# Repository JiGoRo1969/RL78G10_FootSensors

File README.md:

# FootSensors with RL78/G10 software library (Rev.20200416)

This is a project to use Force Sensing Registors with RL78/G10
included with CS+ environment setting files provided by Renesas Electronics Corp.
So you can easily modify and add this codes with CS+ on Windows PC.
  
Let's enjoy it !

## Information for target board

RL78/G10 board "AE-R5F10Y47ASP" is provided by Akizukidenshi in Japan.
  
JPN : http://akizukidenshi.com/catalog/g/gK-09035/

## Installation

Import this project into CS+.

## Usage

The protocol stack is defined with an ICS3.5 provided by KONDO Kagaku.
ICS3.5 uses "Data=8bit, Stop=1bit, Parity=EVEN, baudrate=1.5Mbps."
You will get 4 sensor unit data when master MCU/MPU send 4 bytes data as follows :
|Command|SC|Address|Length|
|-------|--|-------|------|
|0xA0+ID|0x7F|0(fiexed)|4(fiexed)|
  
ID is defined as D_MY_ID in "cg_src/r_cg_userdefine.h".

## Current Support Peripherals

|Function Name        | Pin Name        | notes |
|:--------------------|:---------------:|:------|
|Analog Input         |P02/ANI1         | connecting to one of Force Sensing Registor with pulled up to 3.3V | 
|Analog Input         |P03/ANI2         | connecting to one of Force Sensing Registor with pulled up to 3.3V | 
|Analog Input         |P04/ANI3         | connecting to one of Force Sensing Registor with pulled up to 3.3V | 
|Analog Input         |P05/ANI4         | connecting to one of Force Sensing Registor with pulled up to 3.3V | 
|UART I/F             |P00/TxD0         | connecting to RxD of master MCU/MPU | 
|UART I/F             |P01/RxD0         | connecting to TxD of master MCU/MPU | 
|X'tal                |X1,X2            | mounted on board |
|OCD Debugger I/F     |RESET, TOOL0     | connecting to DEBUGGER |
|Non Connections      |P06, P07, P41    | |
  
You can refer CAD data with Eagle(.brd and .sch) to understand the circuit.
  
|File Name | purpose |
|:--------:|:-------:|
|RL78G10_FOOT_A2.brd| PCB pattern data for pressure sensors with R5F10Y47ASP|
|RL78G10_FOOT_A2.sch| circuit data |
|--------|-------|
|RL78G10_E1.brd| PCB pattern data connecting to E1/E2/E2Lite |
|RL78G10_E1.sch| circuit data |

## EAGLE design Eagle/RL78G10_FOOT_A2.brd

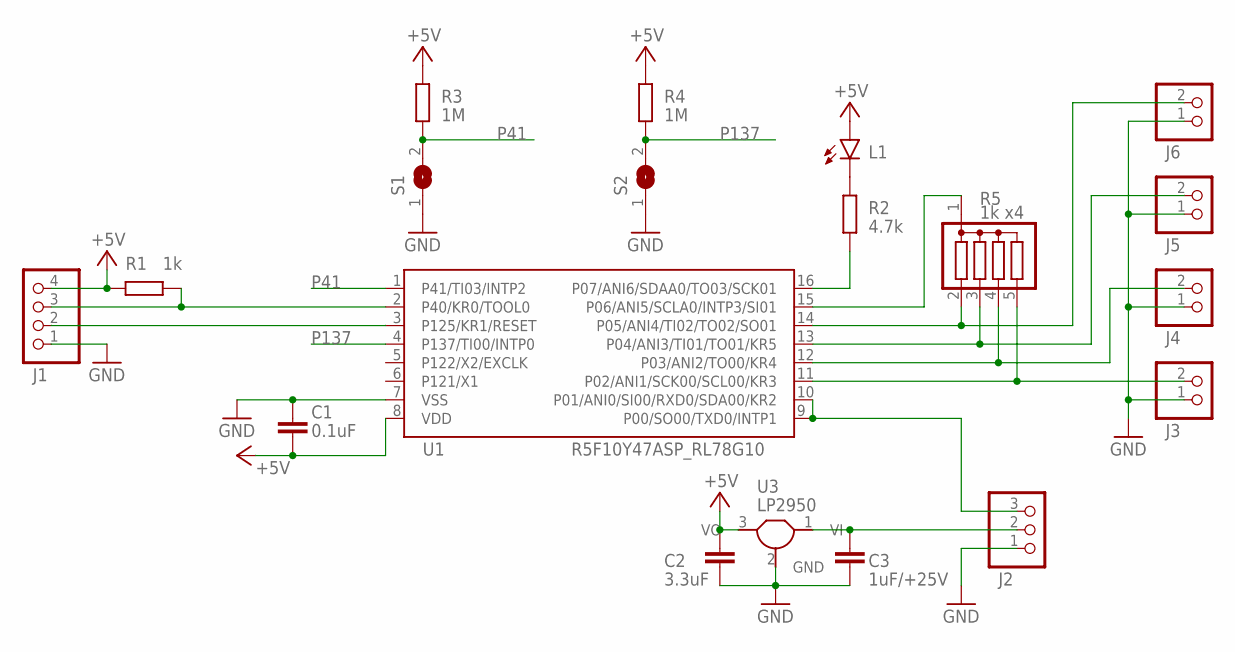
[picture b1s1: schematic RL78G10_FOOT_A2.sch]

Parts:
C1: 0.1uF; C0603
C2: 3.3uF; C0805
C3: 1uF/+25V; C0805
J1: PINHD_1X4; PINHD_1X04
J2: PINHD_1X3; PINHD_1X03
J3, J4, J5, J6: PINHD_1X2; PINHD_1X02
L1: LEDSML0603; SML0603
R1: 1k; R0603
R2: 4.7k; R0603
R3, R4: 1M; R0603
R5: 1k x4; SIL5
S1, S2: SJ-OMINI; SJ-O
U1: R5F10Y47ASP_RL78G10; SSOP16
U3: LP2950; TO92-

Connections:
+5V: C1.2, C2.1, J1.4, L1.A, R1.1, R3.1, R4.1, U1.8 (VDD), U3.3 (VO)
+V: C3.1, J2.2, U3.1 (VI)
ANI1: J3.2, R5.5, U1.11 (P02/ANI1/SCK00/SCL00/KR3)
ANI2: J4.2, R5.4, U1.12 (P03/ANI2/TO00/KR4)
ANI3: J5.2, R5.3, U1.13 (P04/ANI3/TI01/TO01/KR5)
ANI4: J6.2, R5.2, U1.14 (P05/ANI4/TI02/TO02/SO01)
GND: C1.1, C2.2, C3.2, J1.1, J2.1, J3.1, J4.1, J5.1, J6.1, S1.1, S2.1, U1.7 (VSS), U3.2 (GND)
LED: L1.C, R2.1
P06: R5.1, U1.15 (P06/ANI5/SCLA0/INTP3/SI01)
P41: R3.2, S1.2, U1.1 (P41/TI03/INTP2)
P137: R4.2, S2.2, U1.4 (P137/TI00/INTP0)
RESET: J1.2, U1.3 (P125/KR1/RESET)
SIG: J2.3, U1.9 (P00/SO00/TXD0/INTP1), U1.10 (P01/ANI0/SI00/RXD0/SDA00/KR2)
TO03: R2.2, U1.16 (P07/ANI6/SDAA0/TO03/SCK01)
TOOL0: J1.3, R1.2, U1.2 (P40/KR0/TOOL0)

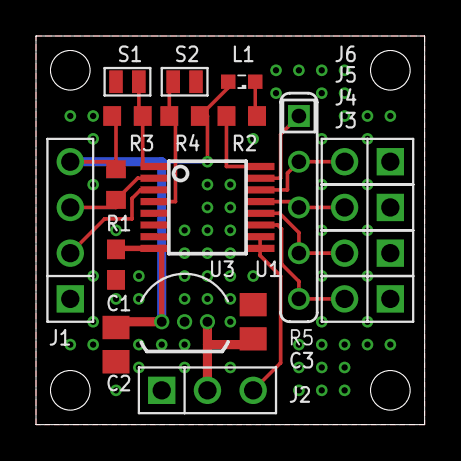
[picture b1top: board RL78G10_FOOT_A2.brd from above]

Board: 2 copper layers, 21.6 x 21.6 mm, 19 parts (0 on the bottom side), 15 nets.

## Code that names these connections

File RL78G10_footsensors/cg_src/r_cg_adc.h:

/***********************************************************************************************************************
* DISCLAIMER
* This software is supplied by Renesas Electronics Corporation and is only intended for use with Renesas products.
* No other uses are authorized. This software is owned by Renesas Electronics Corporation and is protected under all
* applicable laws, including copyright laws. 
* THIS SOFTWARE IS PROVIDED "AS IS" AND RENESAS MAKES NO WARRANTIES REGARDING THIS SOFTWARE, WHETHER EXPRESS, IMPLIED
* OR STATUTORY, INCLUDING BUT NOT LIMITED TO WARRANTIES OF MERCHANTABILITY, FITNESS FOR A PARTICULAR PURPOSE AND
* NON-INFRINGEMENT.  ALL SUCH WARRANTIES ARE EXPRESSLY DISCLAIMED.TO THE MAXIMUM EXTENT PERMITTED NOT PROHIBITED BY
* LAW, NEITHER RENESAS ELECTRONICS CORPORATION NOR ANY OF ITS AFFILIATED COMPANIES SHALL BE LIABLE FOR ANY DIRECT,
* INDIRECT, SPECIAL, INCIDENTAL OR CONSEQUENTIAL DAMAGES FOR ANY REASON RELATED TO THIS SOFTWARE, EVEN IF RENESAS OR
* ITS AFFILIATES HAVE BEEN ADVISED OF THE POSSIBILITY OF SUCH DAMAGES.
* Renesas reserves the right, without notice, to make changes to this software and to discontinue the availability 
* of this software. By using this software, you agree to the additional terms and conditions found by accessing the 
* following link:
* http://www.renesas.com/disclaimer
*
* Copyright (C) 2012, 2019 Renesas Electronics Corporation. All rights reserved.
***********************************************************************************************************************/

/***********************************************************************************************************************
* File Name    : r_cg_adc.h
* Version      : Code Generator for RL78/G10 V1.05.03.02 [20 Nov 2019]
* Device(s)    : R5F10Y47
* Tool-Chain   : CCRL
* Description  : This file implements device driver for ADC module.
* Creation Date: 2020/04/03
***********************************************************************************************************************/
#ifndef ADC_H
#define ADC_H

/***********************************************************************************************************************
Macro definitions (Register bit)
***********************************************************************************************************************/
/*
    Peripheral enable register 0 (PER0)
*/
/* Control of AD converter input clock (ADCEN) */
#define _00_AD_CLOCK_STOP               (0x00U) /* stop supply of input clock */
#define _20_AD_CLOCK_SUPPLY             (0x20U) /* supply input clock */

/*
    AD converter mode register 0 (ADM0)
*/
#define _00_AD_ADM0_INITIALVALUE        (0x00U)
/* AD conversion operation control (ADCS) */
#define _80_AD_CONVERSION_ENABLE        (0x80U) /* enable AD conversion operation control */
#define _00_AD_CONVERSION_DISABLE       (0x00U) /* disable AD conversion operation control */
/* AD conversion clock selection (FR1, FR0) */
#define _00_AD_CONVERSION_CLOCK_8       (0x00U) /* fCLK/8 */
#define _08_AD_CONVERSION_CLOCK_4       (0x08U) /* fCLK/4 */
#define _10_AD_CONVERSION_CLOCK_2       (0x10U) /* fCLK/2 */
#define _18_AD_CONVERSION_CLOCK_1       (0x18U) /* fCLK/1 */
/* Specification AD conversion time mode (LV0) */
#define _00_AD_TIME_MODE_NORMAL_1       (0x00U) /* normal 1 mode */
#define _02_AD_TIME_MODE_NORMAL_2       (0x02U) /* normal 2 mode */
/* AD comparator operation control (ADCE) */
#define _01_AD_COMPARATOR_ENABLE        (0x01U) /* enable comparator operation control */
#define _00_AD_COMPARATOR_DISABLE       (0x00U) /* disable comparator operation control */

/*
    Analog input channel specification register (ADS)
*/
/* Specification of analog input channel (ADS2 - ADS0) */
/* Select mode */
#define _00_AD_INPUT_CHANNEL_0          (0x00U) /* ANI0 */
#define _01_AD_INPUT_CHANNEL_1          (0x01U) /* ANI1 */
#define _02_AD_INPUT_CHANNEL_2          (0x02U) /* ANI2 */
#define _03_AD_INPUT_CHANNEL_3          (0x03U) /* ANI3 */
#define _04_AD_INPUT_CHANNEL_4          (0x04U) /* ANI4 */
#define _05_AD_INPUT_CHANNEL_5          (0x05U) /* ANI5 */
#define _06_AD_INPUT_CHANNEL_6          (0x06U) /* ANI6 */
#define _07_AD_INPUT_INTERREFVOLT       (0x07U) /* internal reference voltage output */

/*
    AD converter mode register 2 (ADM2)
*/
/* AD resolution selection (ADTYP) */
#define _00_AD_RESOLUTION_10BIT         (0x00U) /* 10 bits */
#define _01_AD_RESOLUTION_8BIT          (0x01U) /* 8 bits */

/***********************************************************************************************************************
Macro definitions
***********************************************************************************************************************/

/***********************************************************************************************************************
Typedef definitions
***********************************************************************************************************************/
typedef enum
{
    ADCHANNEL0,
    ADCHANNEL1,
    ADCHANNEL2,
    ADCHANNEL3,
    ADCHANNEL4,
    ADCHANNEL5,
    ADCHANNEL6,
    ADINTERREFVOLT
} ad_channel_t;

/***********************************************************************************************************************
Global functions
***********************************************************************************************************************/
void R_ADC_Create(void);
void R_ADC_Start(void);
void R_ADC_Stop(void);
void R_ADC_Set_OperationOn(void);
void R_ADC_Set_OperationOff(void);
void R_ADC_Get_Result(uint16_t * const buffer);

/* Start user code for function. Do not edit comment generated here */
/* End user code. Do not edit comment generated here */
#endif

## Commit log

2020-05-14 Rev.20200416
2020-06-17 Rev.20200416 with Eagle
